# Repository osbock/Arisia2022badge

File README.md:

# Arisia2022badge
Soldering badge for Arisia 2022

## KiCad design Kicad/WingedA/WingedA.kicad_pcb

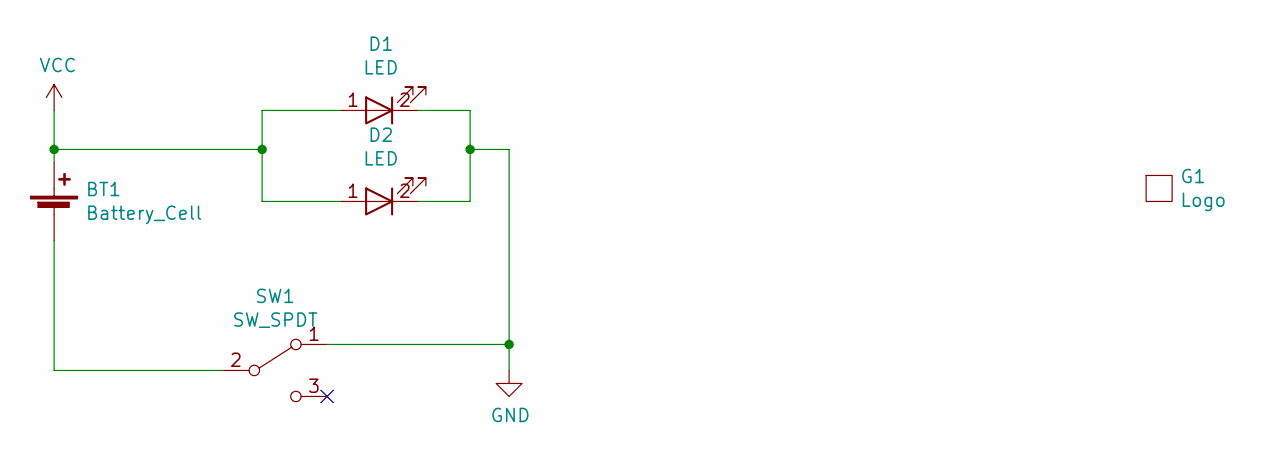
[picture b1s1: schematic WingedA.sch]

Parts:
BT1: Battery_Cell; BK-913
D1, D2: LED; LED_D5.0mm
G1: Logo; WingedA_Logo
SW1: SW_SPDT; SM_SlideSW

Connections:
GND: D1.2 (K), D2.2 (K), SW1.1 (A)
unnamed: BT1.2 (-), SW1.2 (B)
VCC: BT1.1 (+), D1.1 (A), D2.1 (A)

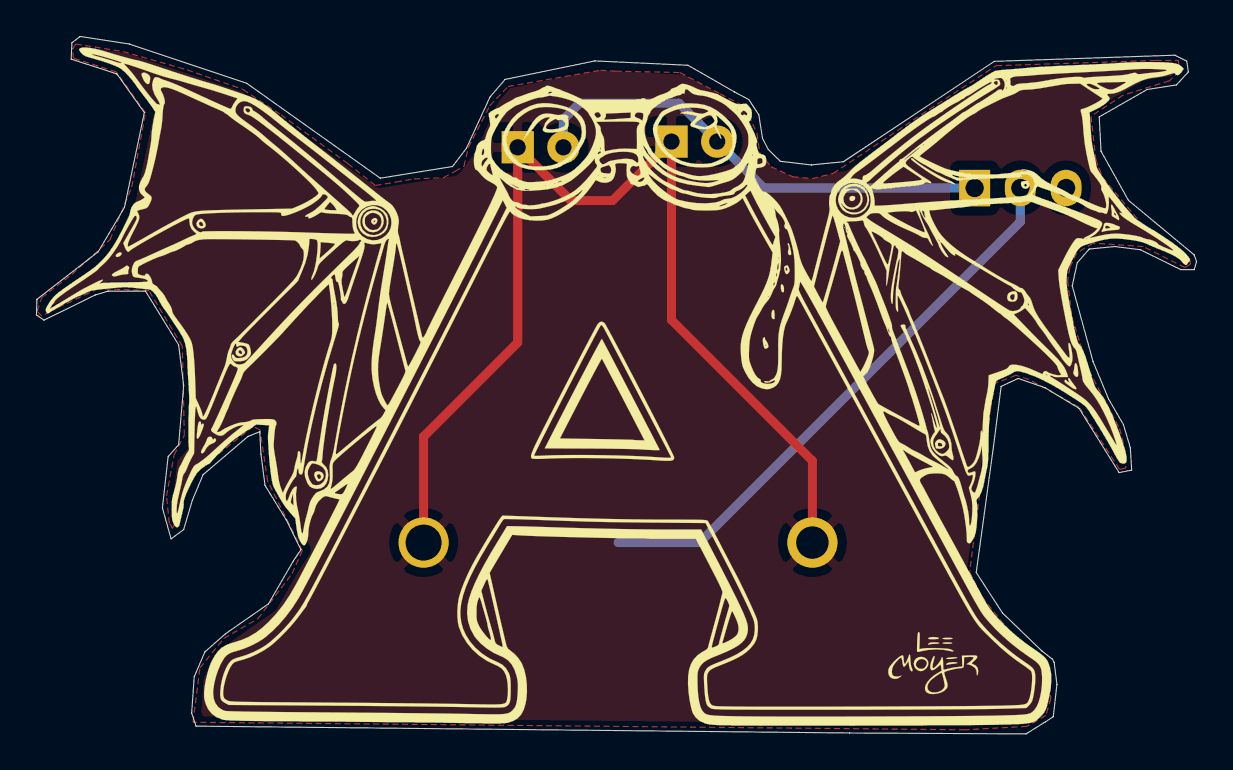
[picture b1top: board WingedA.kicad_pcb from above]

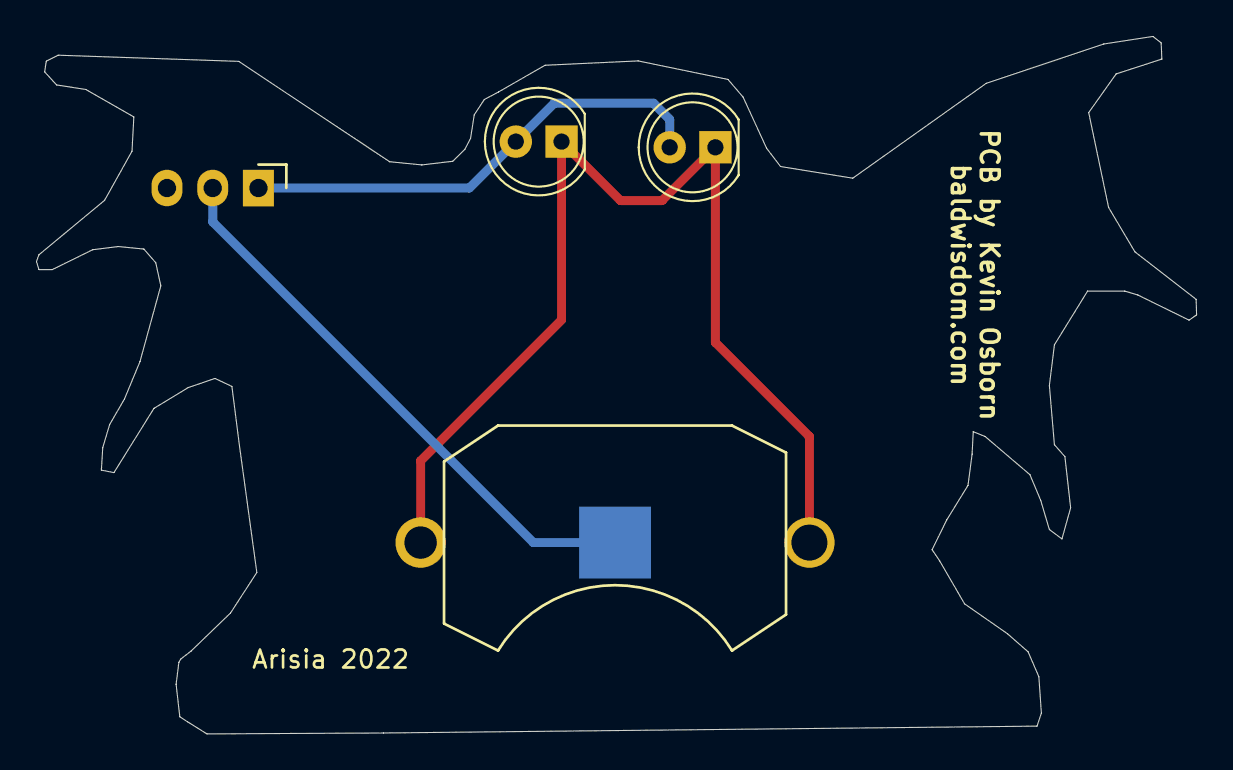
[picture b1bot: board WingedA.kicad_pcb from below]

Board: 2 copper layers, 64.5 x 38.7 mm, 5 parts (4 on the bottom side), 3 nets.

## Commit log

2021-10-17 rev a of badge
